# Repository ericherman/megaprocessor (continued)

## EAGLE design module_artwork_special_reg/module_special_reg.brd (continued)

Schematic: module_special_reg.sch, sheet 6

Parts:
CMP24: BUS_SPLIT_DISPLAY
CMP27, CMP28, CMP29: BUS_CONSTRUCT_DISPLAY; BUS_SPLIT_DISPLAY
CMP31: 2AND

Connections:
ADD2_0: CMP29.P$9 (IN_8); also elsewhere on the board
ADD2_1: CMP29.P$10 (IN_9); also elsewhere on the board
ADD2_2: CMP29.P$11 (IN_10); also elsewhere on the board
ADD2_3: CMP29.P$12 (IN_11); also elsewhere on the board
ADD2_4: CMP29.P$13 (IN_12); also elsewhere on the board
ADD2_5: CMP29.P$14 (IN_13); also elsewhere on the board
ADD2_6: CMP29.P$15 (IN_14); also elsewhere on the board
ADD2_7: CMP29.P$16 (IN_15); also elsewhere on the board
BUS_ALU_OUTPUT: CMP24.INPUT
BUS_ALU_OUTPUT0: CMP24.P$1 (OUT_0), CMP28.P$1 (IN_0)
BUS_ALU_OUTPUT1: CMP24.P$2 (OUT_1), CMP28.P$2 (IN_1)
BUS_ALU_OUTPUT2: CMP24.P$3 (OUT_2), CMP28.P$3 (IN_2)
BUS_ALU_OUTPUT3: CMP24.P$4 (OUT_3), CMP28.P$4 (IN_3)
BUS_ALU_OUTPUT4: CMP24.P$5 (OUT_4), CMP28.P$5 (IN_4)
H_5: CMP28.P$6 (IN_5), CMP29.P$6 (IN_5); also elsewhere on the board
H_6: CMP28.P$7 (IN_6), CMP29.P$7 (IN_6); also elsewhere on the board
H_7: CMP28.P$8 (IN_7), CMP29.P$8 (IN_7); also elsewhere on the board
H_ADDER0: CMP29.P$1 (IN_0); also elsewhere on the board
H_ADDER1: CMP29.P$2 (IN_1); also elsewhere on the board
H_ADDER2: CMP29.P$3 (IN_2); also elsewhere on the board
H_ADDER3: CMP29.P$4 (IN_3); also elsewhere on the board
H_ADDER4: CMP29.P$5 (IN_4); also elsewhere on the board
H_SHIFT_UPDATE_DATA: CMP29.INPUT (OUT); also elsewhere on the board
unnamed: CMP28.P$9 (IN_8), CMP28.P$10 (IN_9), CMP28.P$11 (IN_10), CMP28.P$12 (IN_11), CMP28.P$13 (IN_12), CMP28.P$14 (IN_13), CMP28.P$15 (IN_14), CMP28.P$16 (IN_15)
OPCODE_IS_STACK_REL_GROUP_N: CMP31.P$1 (1); also elsewhere on the board
SHIFT_REG_VALUE: CMP28.INPUT (OUT); also elsewhere on the board
SIGN_EXTEND_READ_DATA: CMP27.INPUT (OUT); also elsewhere on the board
SIGN_EXTEND_VAL: CMP27.P$9 (IN_8), CMP27.P$10 (IN_9), CMP27.P$11 (IN_10), CMP27.P$12 (IN_11), CMP27.P$13 (IN_12), CMP27.P$14 (IN_13), CMP27.P$15 (IN_14), CMP27.P$16 (IN_15), CMP31.OUT_P
ZXT_READ_DATA_0: CMP27.P$1 (IN_0); also elsewhere on the board
ZXT_READ_DATA_1: CMP27.P$2 (IN_1); also elsewhere on the board
ZXT_READ_DATA_2: CMP27.P$3 (IN_2); also elsewhere on the board
ZXT_READ_DATA_3: CMP27.P$4 (IN_3); also elsewhere on the board
ZXT_READ_DATA_4: CMP27.P$5 (IN_4); also elsewhere on the board
ZXT_READ_DATA_5: CMP27.P$6 (IN_5); also elsewhere on the board
ZXT_READ_DATA_6: CMP27.P$7 (IN_6); also elsewhere on the board
ZXT_READ_DATA_7: CMP27.P$8 (IN_7), CMP31.P$2 (2); also elsewhere on the board

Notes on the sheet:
sign_extend_val = Cpnt_2AND(bus_h_wd_reg_ctrl.opcode_is_stack_rel_group_n, bus_zero_extend_read_data[7]);

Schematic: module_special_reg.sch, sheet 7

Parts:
CMP8: WORD_BYTE
CMP12: 2X16MUX
CMP13: 4X16MUX
CMP18: 4DIGIT
CMP20: 16REG
CMP23: BUS_2_BUS; BUS2BUS
CMP30: BUS_CONSTRUCT; BUS_SPLIT

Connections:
BUS_PC_B: CMP12.PORT1; also elsewhere on the board
BUS_PS: CMP13.PORT3; also elsewhere on the board
BUS_RA: CMP12.PORT0; also elsewhere on the board
unnamed: CMP8.SRC, CMP12.OUT (OUTPUT)
unnamed: CMP8.MSB_1, CMP13.PORT1
unnamed: CMP8.LSB_1, CMP13.PORT2
unnamed: CMP13.PORT0, CMP30.INPUT (OUT)
unnamed: CMP30.P$1 (IN_0), CMP30.P$2 (IN_1), CMP30.P$3 (IN_2), CMP30.P$4 (IN_3), CMP30.P$5 (IN_4), CMP30.P$6 (IN_5), CMP30.P$7 (IN_6), CMP30.P$8 (IN_7), CMP30.P$9 (IN_8), CMP30.P$10 (IN_9), CMP30.P$11 (IN_10), CMP30.P$12 (IN_11), CMP30.P$13 (IN_12), CMP30.P$14 (IN_13), CMP30.P$15 (IN_14), CMP30.P$16 (IN_15)
unnamed: CMP13.PORTOUT (OUTPUT), CMP20.INPUT (IN)
unnamed: CMP18.P$1, CMP20.DISPLAY (DSP)
unnamed: CMP20.OUT, CMP23.P$1 (IN)
NEXT_WR_DATA_MUX_PC_RA_LSB: CMP13.EN2; also elsewhere on the board
NEXT_WR_DATA_MUX_PC_RA_MSB: CMP13.EN1; also elsewhere on the board
NEXT_WR_DATA_MUX_PS: CMP13.EN3; also elsewhere on the board
NEXT_WR_DATA_WIDE_MUX_PC: CMP12.EN1; also elsewhere on the board
NEXT_WR_DATA_WIDE_MUX_RA: CMP12.EN0; also elsewhere on the board

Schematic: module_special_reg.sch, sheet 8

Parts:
CMP15: BUS_4TEE
CMP35: 4X16MUX
CMP38: 16REG
CMP39: 4DIGIT
CMP42: BUS_2_BUS; BUS2BUS
CMP45: BUS_TEE
CMP50: BUS_CONSTRUCT; BUS_SPLIT

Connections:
BUS_ADD2_A: CMP35.PORT1; also elsewhere on the board
BUS_MEMORY_READ_WORD_B: CMP35.PORT2; also elsewhere on the board
BUS_NEXT_PC: CMP45.OUTB (B); also elsewhere on the board
BUS_PC_A: CMP15.3, CMP35.PORT3
BUS_PC_B: CMP15.4; also elsewhere on the board
unnamed: CMP50.P$1 (IN_0), CMP50.P$2 (IN_1)
unnamed: CMP35.PORTOUT (OUTPUT), CMP45.INPUT (IN)
unnamed: CMP38.DISPLAY (DSP), CMP39.P$1
unnamed: CMP15.SRC, CMP38.OUT
unnamed: CMP15.1, CMP42.P$1 (IN)
unnamed: CMP38.INPUT (IN), CMP45.OUT_A (A)
unnamed: CMP50.P$5 (IN_4), CMP50.P$6 (IN_5), CMP50.P$7 (IN_6), CMP50.P$8 (IN_7), CMP50.P$9 (IN_8), CMP50.P$10 (IN_9), CMP50.P$11 (IN_10), CMP50.P$12 (IN_11), CMP50.P$13 (IN_12), CMP50.P$14 (IN_13), CMP50.P$15 (IN_14), CMP50.P$16 (IN_15)
NEXT_PC_MUX_ADD2: CMP35.EN1; also elsewhere on the board
NEXT_PC_MUX_HOLD: CMP35.EN3; also elsewhere on the board
NEXT_PC_MUX_H_AND_DATA: CMP35.EN2; also elsewhere on the board
TRAP_STATE_7: CMP35.EN0; also elsewhere on the board
VECTOR_CODE_0: CMP50.P$3 (IN_2); also elsewhere on the board
VECTOR_CODE_1: CMP50.P$4 (IN_3); also elsewhere on the board
VECTOR_VALUE: CMP35.PORT0, CMP50.INPUT (OUT)

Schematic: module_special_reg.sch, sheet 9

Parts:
CMP51: 2X16MUX
CMP52, CMP57: 16REG
CMP53, CMP58: 4DIGIT
CMP54: BUS_TEE
CMP55, CMP59: BUS_2_BUS; BUS2BUS
CMP56: 4X16MUX

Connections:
BUS_ADD2_B: CMP51.PORT1; also elsewhere on the board
BUS_ADD2_C: CMP56.PORT1; also elsewhere on the board
BUS_MEMORY_READ_WORD_A: CMP56.PORT2; also elsewhere on the board
BUS_NEXT_PC: CMP56.PORT3; also elsewhere on the board
BUS_RI: CMP56.PORT0; also elsewhere on the board
unnamed: CMP51.OUT (OUTPUT), CMP52.INPUT (IN)
unnamed: CMP52.DISPLAY (DSP), CMP53.P$1
unnamed: CMP52.OUT, CMP54.INPUT (IN)
unnamed: CMP56.PORTOUT (OUTPUT), CMP57.INPUT (IN)
unnamed: CMP57.DISPLAY (DSP), CMP58.P$1
unnamed: CMP57.OUT, CMP59.P$1 (IN)
NEXT_ADDR_MUX_ADD2: CMP56.EN1; also elsewhere on the board
NEXT_ADDR_MUX_PC: CMP56.EN3; also elsewhere on the board
NEXT_ADDR_MUX_READ_WORD: CMP56.EN2; also elsewhere on the board
NEXT_ADDR_MUX_RI: CMP56.EN0; also elsewhere on the board
NEXT_SP_MUX_ADD2: CMP51.EN1; also elsewhere on the board
NEXT_SP_MUX_HOLD: CMP51.EN0; also elsewhere on the board
REG_SP_A: CMP51.PORT0, CMP54.OUT_A (A)
REG_SP_B: CMP54.OUTB (B), CMP55.P$1 (IN)

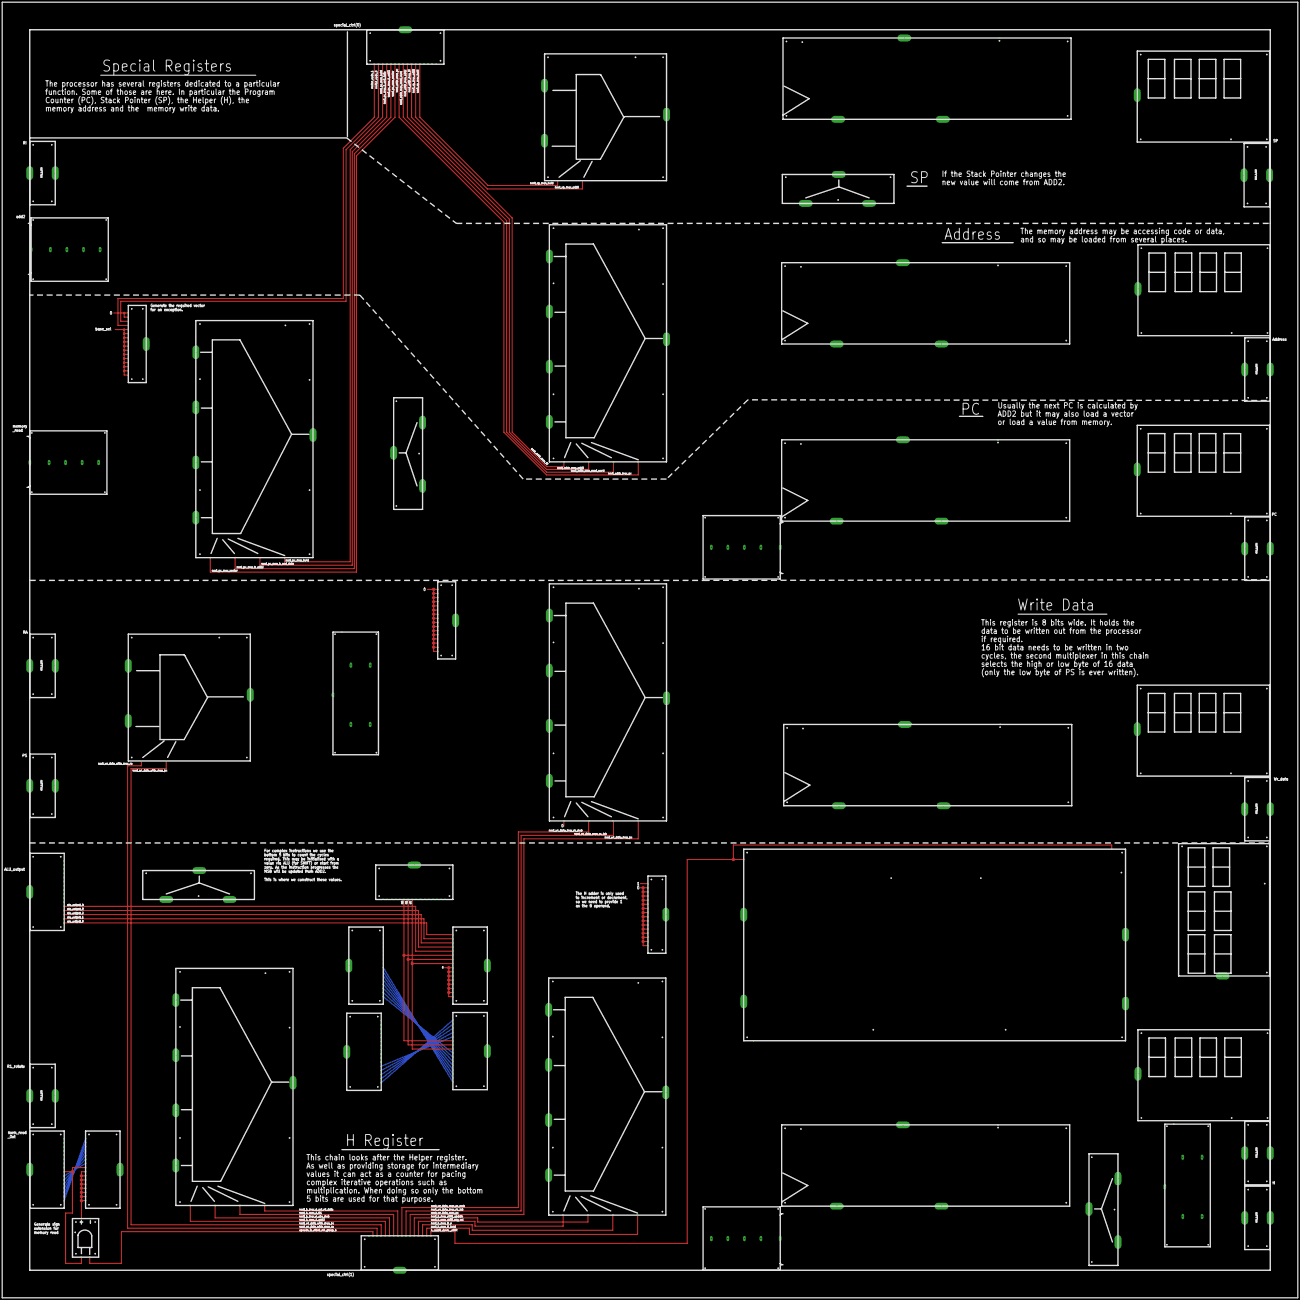
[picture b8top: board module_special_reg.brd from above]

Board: 2 copper layers, 1193.8 x 1193.8 mm, 53 parts (0 on the bottom side), 116 nets.
